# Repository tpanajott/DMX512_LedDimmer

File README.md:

# DMX512 Controller with remote LED drivers
This is a wireless DMX512 controller that will accept input of channel data via MQTT, web interface or manual control of a channel via button input. It has built in support for MQTT auto-registration in Home Assistant. The controller can take up to four inputs for buttons that can control 4 channels of DMX data. Each LED Driver board is configured to drive 350mA LEDs and each LED Driver board can be configured for a channel separately.

# Features
* Auto-registration of channels to Home Assistant via MQTT.
* Setup AP to configure parameters to connect to WiFi.
* Web interface to dynamically configured all settings without changing the code.
* Multiple buttons can control the same channel.
* Many settings for controlling dimming behaviour.
* Control of up to 4 different channels of lights.

# Settings
|Setting|Description|
|--------|-----------|
|Device name|Used as WiFi hostname, MQTT client name and as "device name" in Home Assistant.|
|Serial log level|The desired log level for serial output. Simply leave at "Error" or "None" when installed as no serial monitor will be there to capture it.|
|Connect to WiFi|The WiFi SSID (WiFi name) to connect to. Bu pressing the "List"-button a list of all available networks can be shown and a network selected.|
|WiFi Password|The password (PSK) for the chosen WiFi.|
|Minimum button press time|The time, in milliseconds, a button must have the same state before it is considered a press.|
|Time before dimming|The maximum time for a button to be considered a "press". If the button is still held after this amount if time the channel will start dimming.|

## Channel Settings
|Setting|Description|
|--------|-----------|
|Slider|The slider can be used to control brightness directly from the web interface.|
|Enabled|Wether the channel is in use or not.|
|Name|This is used as the light name in Home Assistant.|
|Channel|The DMX channel to send data on. This must match the "slave" card that is connected to the actual LEDs.|
|Minimum Level|Many LEDs simply don't light below to low a voltage. This setting will force at least the light level as the minimum. By using the slider for the channel and noting the value in "Current Output" this value can be found quiet easily.|
|Maximum Level|The maximum light level.|
|Dimming Speed|The time, in milliseconds, between each step up/down when dimming via a button input.|
|Auto-Dimming Speed|The time, in milliseconds, between each step up/down when dimming via web interface or MQTT.|
|Hold Period|The time, in milliseconds, to wait at min/max positions before switching direction and dimming again.|

## Button Settings
|Setting|Description|
|--------|-----------|
|Enabled|Used to enabling checking of button input.|
|Channel|This must match a configured channel in the "DMX Channels"-section. This is the DMX-channel to control.|

## MQTT Settings
|Setting|Description|
|--------|-----------|
|MQTT Server|The address to the MQTT server to be used.|
|MQTT Port|The port of the MQTT server.|
|MQTT Base Topic|The configured MQTT topic for Home Assistant to listen on. The default in Home Assistant is "homeassistant/".|
|Used MQTT authenticaion?|Check if using username and password for authentication to MQTT server.|
|MQTT Username|The username to use for login at the MQTT server.|
|MQTT Password|The password to use for login at the MQTT server.|

## Images
### Web Interface

### Controller board

### LED Driver board

## Bugs
* Input for Button 3 does not work. This needs a redesign of the PCB and for it to use an other GPIO input.

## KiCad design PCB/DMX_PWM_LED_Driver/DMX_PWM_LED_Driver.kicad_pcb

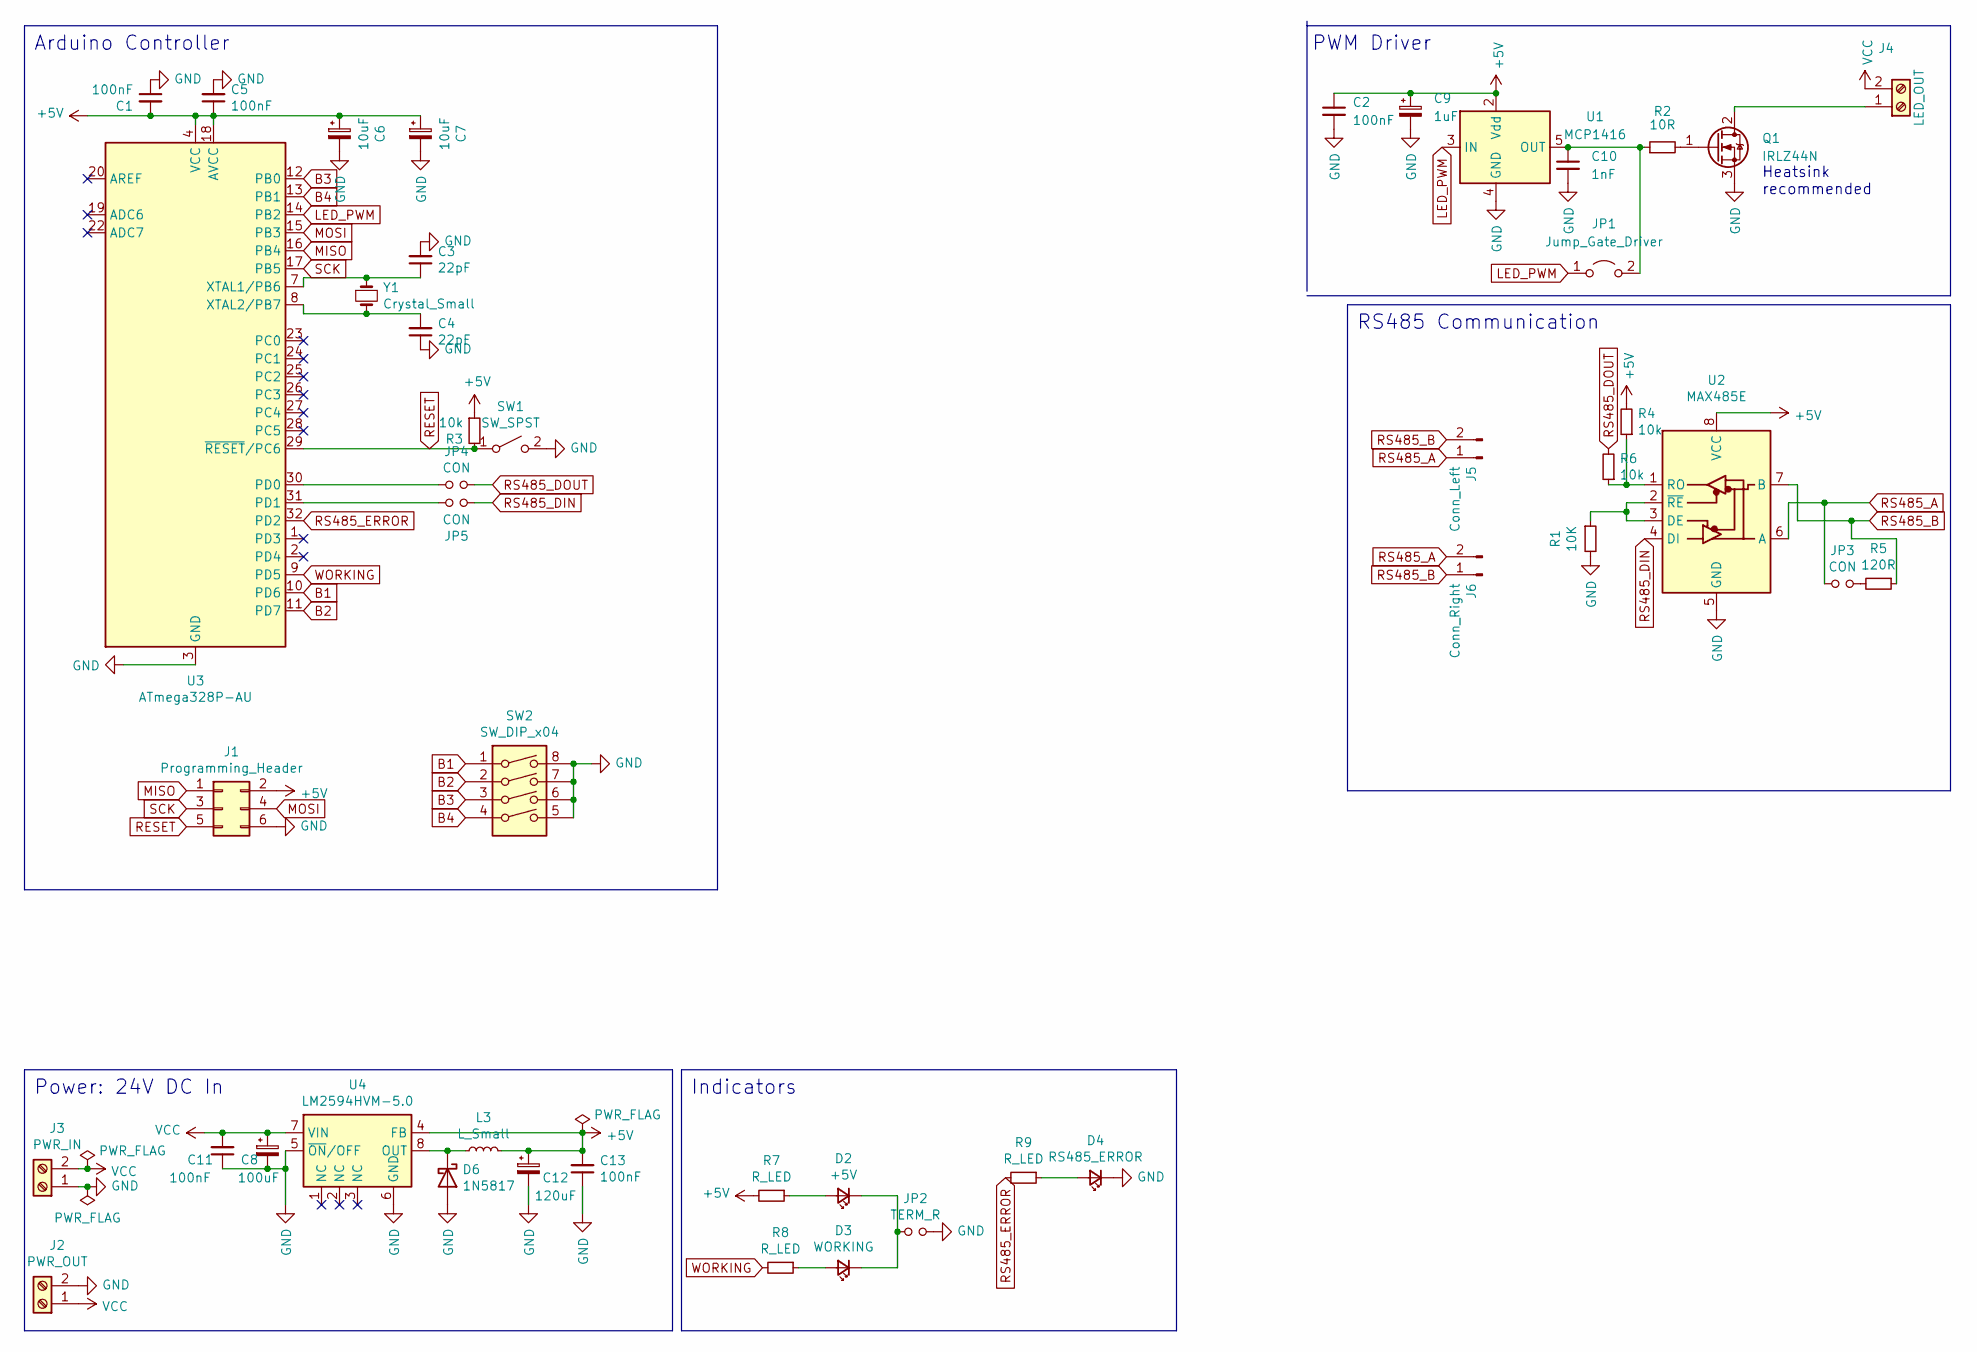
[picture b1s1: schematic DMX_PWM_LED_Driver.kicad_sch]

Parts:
C1, C5, C11, C13: 100nF; C_0805_2012Metric_Pad1.18x1.45mm_HandSolder; LCSC C49678
C2: 100nF; C_0805_2012Metric; LCSC C519929
C3, C4: 22pF; C_0805_2012Metric_Pad1.18x1.45mm_HandSolder; LCSC C24658
C6, C7: 10uF; CP_Radial_D4.0mm_P1.50mm; LCSC C694328
C8: 100uF; CP_Radial_D6.3mm_P2.50mm; LCSC C47859
C9: 1uF; CP_Radial_D5.0mm_P2.00mm; LCSC C62934
C10: 1nF; C_0603_1608Metric; LCSC C77026
C12: 120uF; CP_Radial_D8.0mm_P3.50mm; LCSC C178703
D2: +5V; D_1206_3216Metric_Pad1.42x1.75mm_HandSolder
D3: WORKING; D_1206_3216Metric_Pad1.42x1.75mm_HandSolder
D4: RS485_ERROR; D_1206_3216Metric_Pad1.42x1.75mm_HandSolder
D6: 1N5817; D_SOD-123; LCSC C727113
J1: Programming_Header; IDC-Header_2x03_P2.54mm_Vertical; LCSC C11214
J2: PWR_OUT; TerminalBlock_Phoenix_MKDS-1,5-2_1x02_P5.00mm_Horizontal; LCSC C8404
J3: PWR_IN; TerminalBlock_Phoenix_MKDS-1,5-2_1x02_P5.00mm_Horizontal; LCSC C8404
J4: LED_OUT; TerminalBlock_Phoenix_MKDS-1,5-2_1x02_P5.00mm_Horizontal; LCSC C8404
J5: Conn_Left; JST_XH_B2B-XH-A_1x02_P2.50mm_Vertical
J6: Conn_Right; JST_XH_B2B-XH-A_1x02_P2.50mm_Vertical
JP1: Jump_Gate_Driver; SolderJumper-2_P1.3mm_Open_Pad1.0x1.5mm
JP2: TERM_R; PinHeader_1x02_P2.54mm_Vertical; LCSC C234182
JP3, JP4, JP5: CON; PinHeader_1x02_P2.54mm_Vertical; LCSC C234182
L3: L_Small; L_6.3x6.3_H3; LCSC C206230
Q1: IRLZ44N; TO-220-3_Vertical
R1: 10K; R_0805_2012Metric_Pad1.20x1.40mm_HandSolder; LCSC C25612
R2: 10R; R_0805_2012Metric; LCSC C25278
R3, R4, R6: 10k; R_0805_2012Metric_Pad1.20x1.40mm_HandSolder; LCSC C25612
R5: 120R; R_0805_2012Metric_Pad1.20x1.40mm_HandSolder; LCSC C966144
R7, R8, R9: R_LED; R_1206_3216Metric_Pad1.30x1.75mm_HandSolder
SW1: SW_SPST; SW_Push_SPST_NO_Alps_SKRK
SW2: SW_DIP_x04; SW_DIP_SPSTx04_Slide_6.7x11.72mm_W8.61mm_P2.54mm_LowProfile; LCSC C54950
U1: MCP1416; SOT-23-5; LCSC C83775
U2: MAX485E; SOIC-8_3.9x4.9mm_P1.27mm; LCSC C19738
U3: ATmega328P-AU; TQFP-32_7x7mm_P0.8mm; LCSC C14877
U4: LM2594HVM-5.0; SOIC-8_3.9x4.9mm_P1.27mm; LCSC C179674
Y1: Crystal_Small; Crystal_HC49-U_Vertical; LCSC C16212

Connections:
+5V: C1.2, C2.1, C5.1, C6.1, C7.1, C9.1, C12.1, C13.2, J1.2, L3.2, R3.1, R4.2, R7.2, U1.2 (Vdd), U2.8 (VCC), U3.4 (VCC), U3.6 (VCC), U3.18 (AVCC), U4.4 (FB)
B1: SW2.1, U3.10 (PD6)
B2: SW2.2, U3.11 (PD7)
B3: SW2.3, U3.12 (PB0)
B4: SW2.4, U3.13 (PB1)
GND: C1.1, C2.2, C3.2, C4.1, C5.2, C6.2, C7.2, C8.2, C9.2, C10.2, C11.1, C12.2, C13.1, D4.1 (K), D6.2 (A), J1.6, J2.2, J3.1, JP2.2, Q1.3 (S), R1.2, SW1.2 (B), SW2.5, SW2.6, SW2.7, SW2.8, U1.4 (GND), U2.5 (GND), U3.3 (GND), U3.5 (GND), U3.21 (GND), U4.5 (~ON/OFF), U4.6 (GND)
LED_PWM: JP1.1 (A), U1.3 (IN), U3.14 (PB2)
MISO: J1.1, U3.16 (PB4)
MOSI: J1.4, U3.15 (PB3)
unnamed: C3.1, U3.7 (XTAL1/PB6), Y1.1
unnamed: C4.2, U3.8 (XTAL2/PB7), Y1.2
unnamed: C10.1, JP1.2 (B), R2.1, U1.5 (OUT)
unnamed: D2.1 (K), D3.1 (K), JP2.1
unnamed: D2.2 (A), R7.1
unnamed: D3.2 (A), R8.1
unnamed: D4.2 (A), R9.1
unnamed: D6.1 (K), L3.1, U4.8 (OUT)
unnamed: J4.1, Q1.2 (D)
unnamed: JP3.2, R5.2
unnamed: JP4.1, U3.30 (PD0)
unnamed: JP5.2, U3.31 (PD1)
unnamed: Q1.1 (G), R2.2
unnamed: R1.1, U2.2 (~RE), U2.3 (DE)
unnamed: R4.1, R6.1, U2.1 (RO)
RESET: J1.5, R3.2, SW1.1 (A), U3.29 (~RESET/PC6)
RS485_A: J5.1, J6.2, JP3.1, U2.6 (A)
RS485_B: J5.2, J6.1, R5.1, U2.7 (B)
RS485_DIN: JP5.1, U2.4 (DI)
RS485_DOUT: JP4.2, R6.2
RS485_ERROR: R9.2, U3.32 (PD2)
SCK: J1.3, U3.17 (PB5)
VCC: C8.1, C11.2, J2.1, J3.2, J4.2, U4.7 (VIN)
WORKING: R8.2, U3.9 (PD5)

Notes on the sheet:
RS485 Communication
Arduino Controller
Indicators
Power: 24V DC In
PWM Driver
Heatsink recommended

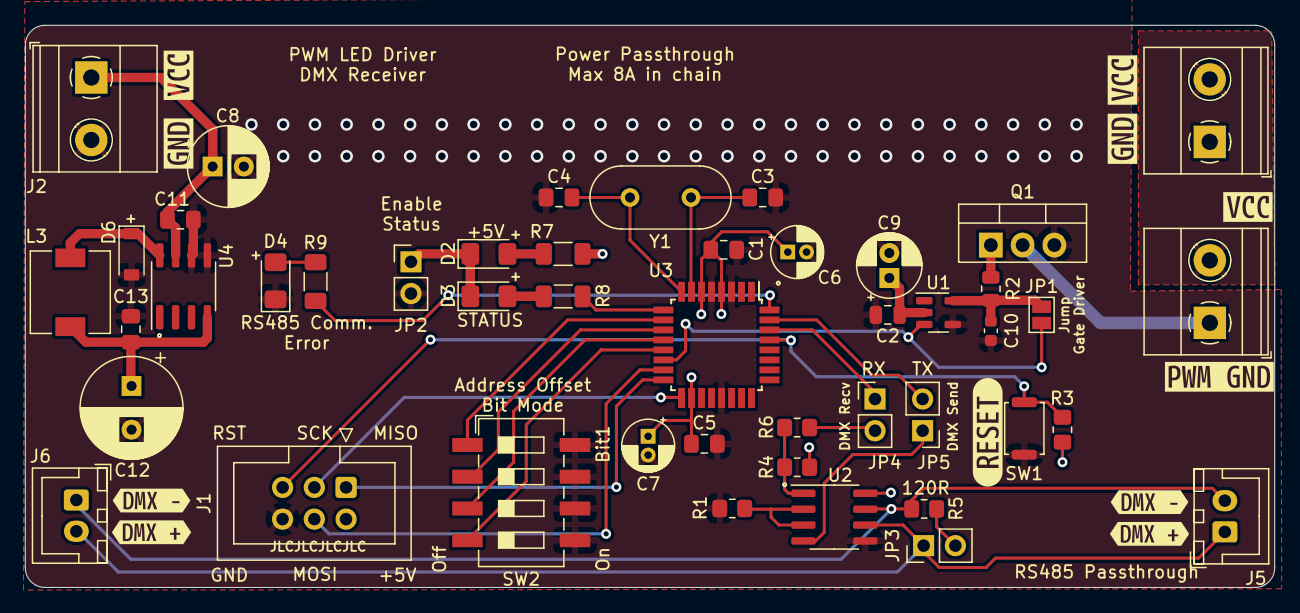
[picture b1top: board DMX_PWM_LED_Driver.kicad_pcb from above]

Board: 2 copper layers, 100.0 x 45.0 mm, 57 parts (0 on the bottom side), 33 nets.

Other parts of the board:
kibuzzard-63E822D9: G***; kibuzzard-63E822D9
kibuzzard-63E822E4, kibuzzard-63E822E4#2, kibuzzard-63E822E4#3: G***; kibuzzard-63E822E4
kibuzzard-63E8231D, kibuzzard-63E8231D#2: G***; kibuzzard-63E8231D
kibuzzard-63E8236A, kibuzzard-63E8236A#2: G***; kibuzzard-63E8236A
kibuzzard-63E8237A, kibuzzard-63E8237A#2: G***; kibuzzard-63E8237A
kibuzzard-63E8252B: G***; kibuzzard-63E8252B

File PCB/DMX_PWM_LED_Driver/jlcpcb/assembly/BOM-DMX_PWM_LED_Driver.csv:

Comment,Designator,Footprint,LCSC
Programming_Header,J1,IDC-Header_2x03_P2.54mm_Vertical,C11214
ATmega328P-AU,U3,TQFP-32_7x7mm_P0.8mm,C14877
Crystal_Small,Y1,Crystal_HC49-U_Vertical,C16212
120uF,C12,CP_Radial_D8.0mm_P3.50mm,C178703
LM2594HVM-5.0,U4,SOIC-8_3.9x4.9mm_P1.27mm,C179674
MAX485E,U2,SOIC-8_3.9x4.9mm_P1.27mm,C19738
L_Small,L3,L_6.3x6.3_H3,C206230
TERM_R,"JP2,JP3,JP4,JP5",PinHeader_1x02_P2.54mm_Vertical,C234182
22pF,"C3,C4",C_0805_2012Metric_Pad1.18x1.45mm_HandSolder,C24658
10R,R2,R_0805_2012Metric,C25278
10K,"R1,R3,R4,R6",R_0805_2012Metric_Pad1.20x1.40mm_HandSolder,C25612
100uF,C8,CP_Radial_D6.3mm_P2.50mm,C47859
100nF,"C1,C11,C13,C5",C_0805_2012Metric_Pad1.18x1.45mm_HandSolder,C49678
100nF,C2,C_0805_2012Metric,C519929
SW_DIP_x04,SW2,SW_DIP_SPSTx04_Slide_6.7x11.72mm_W8.61mm_P2.54mm_LowProfile,C54950
1uF,C9,CP_Radial_D5.0mm_P2.00mm,C62934
10uF,"C6,C7",CP_Radial_D4.0mm_P1.50mm,C694328
1N5817,D6,D_SOD-123,C727113
1nF,C10,C_0603_1608Metric,C77026
MCP1416,U1,SOT-23-5,C83775
PWR_OUT,"J2,J3,J4","TerminalBlock_Phoenix_MKDS-1,5-2_1x02_P5.00mm_Horizontal",C8404
120R,R5,R_0805_2012Metric_Pad1.20x1.40mm_HandSolder,C966144
SW_SPST,SW1,SW_Push_SPST_NO_Alps_SKRK,
Conn_Right,J6,JST_XH_B2B-XH-A_1x02_P2.50mm_Vertical,
Conn_Left,J5,JST_XH_B2B-XH-A_1x02_P2.50mm_Vertical,
R_LED,R9,R_1206_3216Metric_Pad1.30x1.75mm_HandSolder,
+5V,D2,D_1206_3216Metric_Pad1.42x1.75mm_HandSolder,
WORKING,D3,D_1206_3216Metric_Pad1.42x1.75mm_HandSolder,
R_LED,R7,R_1206_3216Metric_Pad1.30x1.75mm_HandSolder,
R_LED,R8,R_1206_3216Metric_Pad1.30x1.75mm_HandSolder,
RS485_ERROR,D4,D_1206_3216Metric_Pad1.42x1.75mm_HandSolder,
Jump_Gate_Driver,JP1,SolderJumper-2_P1.3mm_Open_Pad1.0x1.5mm,
IRLZ44N,Q1,TO-220-3_Vertical,

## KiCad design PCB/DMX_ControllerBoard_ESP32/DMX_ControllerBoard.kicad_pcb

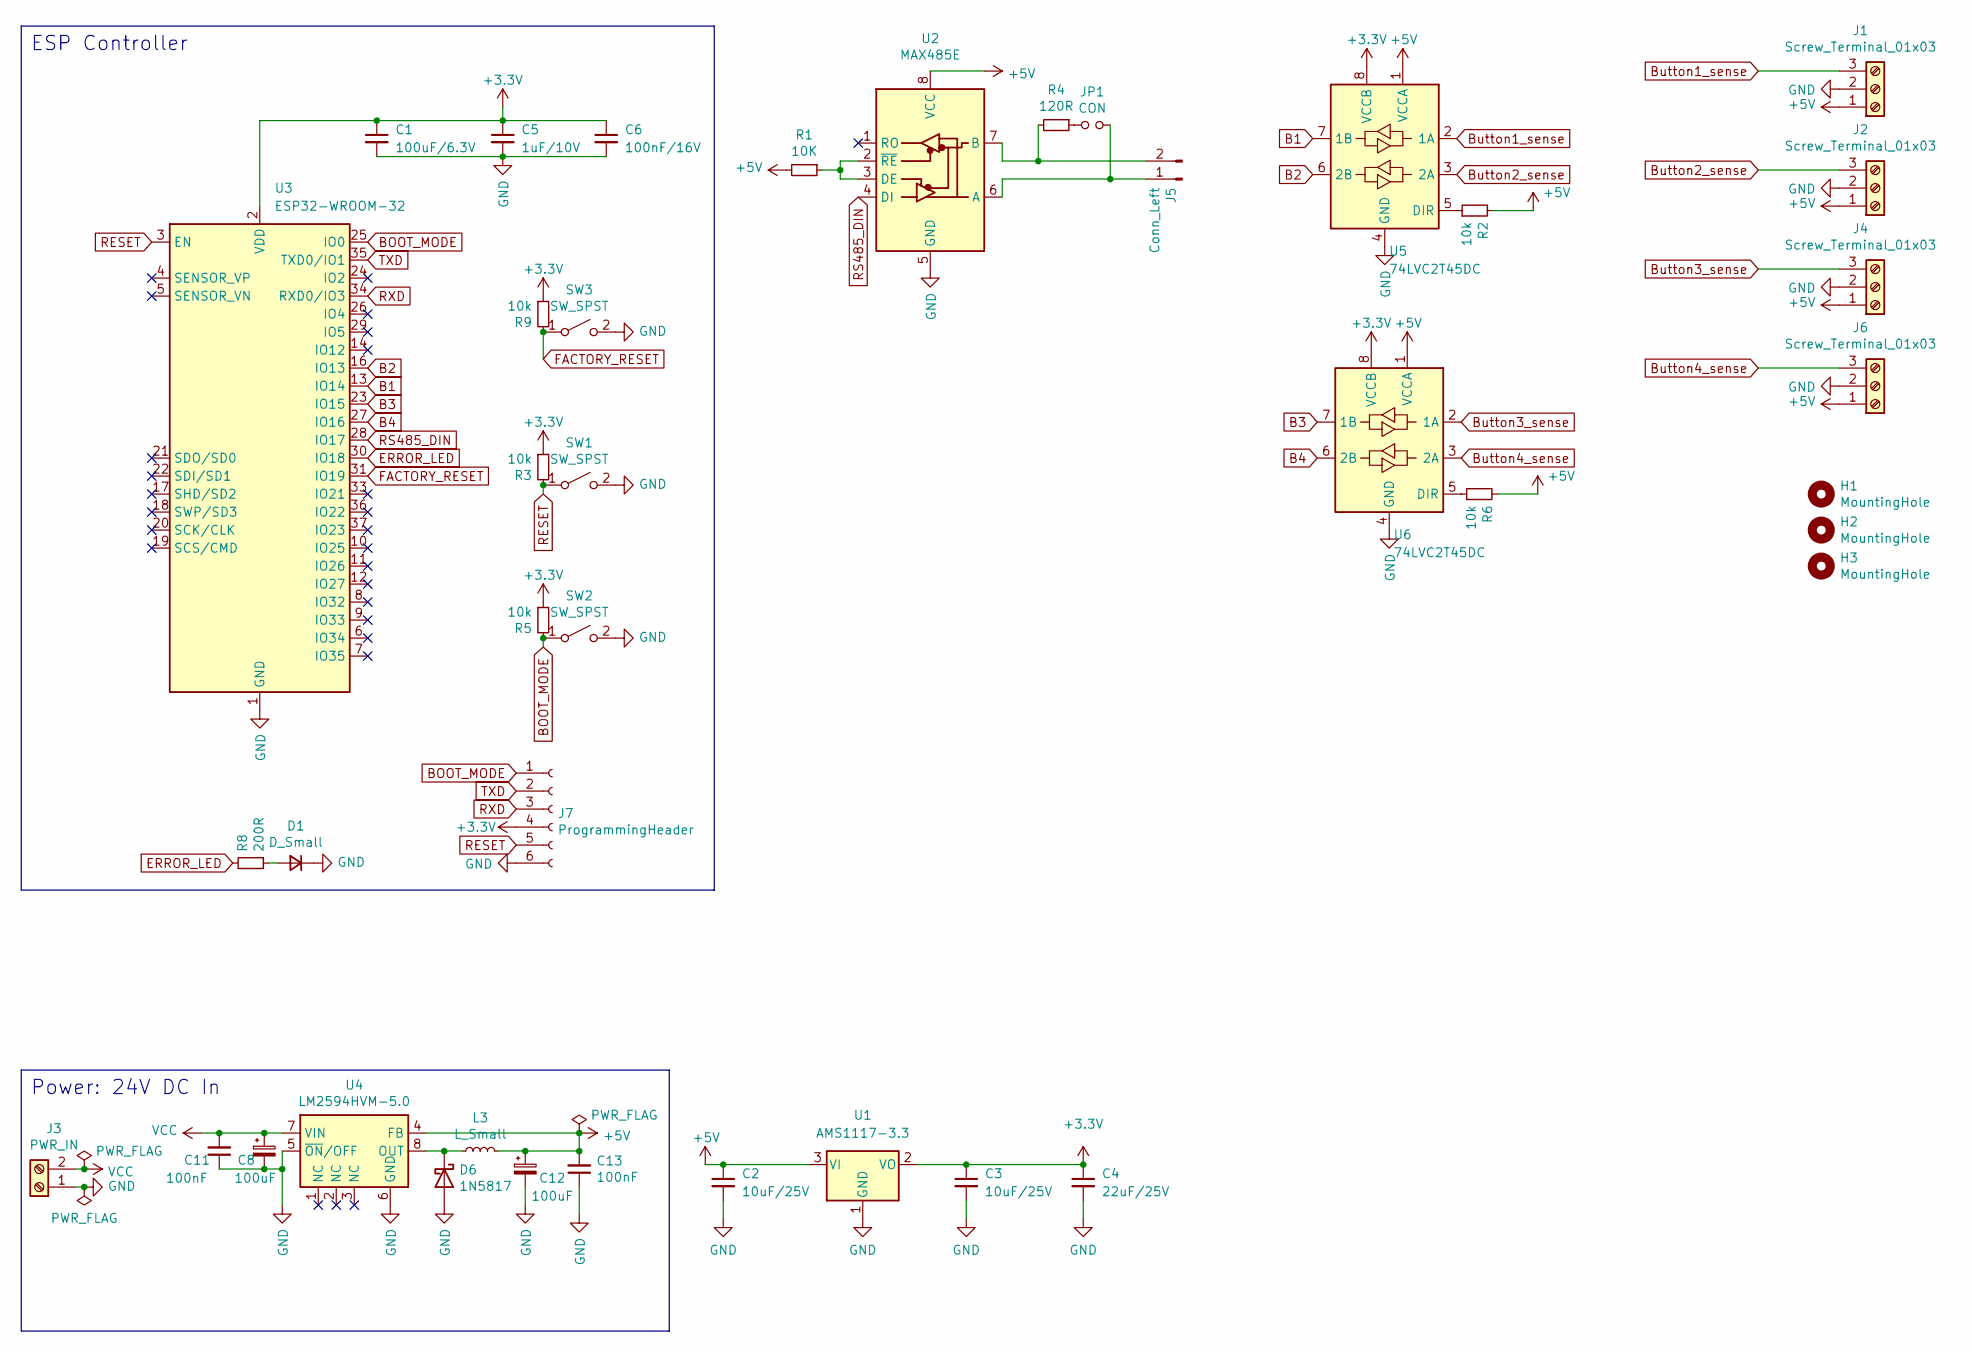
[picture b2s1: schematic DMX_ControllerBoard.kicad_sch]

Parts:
C1: 100uF/6.3V; C_1206_3216Metric; LCSC C15008
C2, C3: 10uF/25V; C_0805_2012Metric; LCSC C2922480
C4: 22uF/25V; C_0805_2012Metric; LCSC C602037
C5: 1uF/10V; C_0805_2012Metric; LCSC C92812
C6: 100nF/16V; C_0805_2012Metric; LCSC C519929
C8: 100uF; CP_Radial_D6.3mm_P2.50mm; LCSC C47859
C11, C13: 100nF; C_0805_2012Metric_Pad1.18x1.45mm_HandSolder; LCSC C49678
C12: 100uF; CP_Radial_D8.0mm_P3.50mm; LCSC C178703
D1: D_Small; D_1206_3216Metric_Pad1.42x1.75mm_HandSolder
D6: 1N5817; D_SOD-123; LCSC C727113
H1, H2, H3: MountingHole; MountingHole_3.2mm_M3
J1, J2, J4, J6: Screw_Terminal_01x03; TerminalBlock_Phoenix_MKDS-3-3-5.08_1x03_P5.08mm_Horizontal; LCSC C72334
J3: PWR_IN; TerminalBlock_Phoenix_MKDS-1,5-2_1x02_P5.00mm_Horizontal; LCSC C8404
J5: Conn_Left; JST_XH_B2B-XH-A_1x02_P2.50mm_Vertical
J7: ProgrammingHeader; PinSocket_1x06_P2.54mm_Vertical
JP1: CON; PinHeader_1x02_P2.54mm_Vertical; LCSC C234182
L3: L_Small; L_6.3x6.3_H3; LCSC C206230
R1: 10K; R_0805_2012Metric_Pad1.20x1.40mm_HandSolder; LCSC C25612
R2, R3, R5, R6, R9: 10k; R_0805_2012Metric_Pad1.20x1.40mm_HandSolder; LCSC C25612
R4: 120R; R_0805_2012Metric_Pad1.20x1.40mm_HandSolder; LCSC C966144
R8: 200R; R_1206_3216Metric_Pad1.30x1.75mm_HandSolder
SW1, SW2, SW3: SW_SPST; SW_Push_SPST_NO_Alps_SKRK
U1: AMS1117-3.3; SOT-223-3_TabPin2; LCSC C2891839
U2: MAX485E; SOIC-8_3.9x4.9mm_P1.27mm; LCSC C19738
U3: ESP32-WROOM-32
U4: LM2594HVM-5.0; SOIC-8_3.9x4.9mm_P1.27mm; LCSC C179674
U5, U6: 74LVC2T45DC; VSSOP-8_2.3x2mm_P0.5mm; LCSC C730237

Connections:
+3.3V: C1.1, C3.1, C4.1, C5.1, C6.1, J7.4, R3.1, R5.1, R9.1, U1.2 (VO), U3.2 (VDD), U5.8 (VCCB), U6.8 (VCCB)
+5V: C2.1, C12.1, C13.2, J1.1, J2.1, J4.1, J6.1, L3.2, R1.2, R2.2, R6.2, U1.3 (VI), U2.8 (VCC), U4.4 (FB), U5.1 (VCCA), U6.1 (VCCA)
B1: U3.13 (IO14), U5.7 (1B)
B2: U3.16 (IO13), U5.6 (2B)
B3: U3.23 (IO15), U6.7 (1B)
B4: U3.27 (IO16), U6.6 (2B)
BOOT_MODE: J7.1, R5.2, SW2.1 (A), U3.25 (IO0)
Button1_sense: J1.3, U5.2 (1A)
Button2_sense: J2.3, U5.3 (2A)
Button3_sense: J4.3, U6.2 (1A)
Button4_sense: J6.3, U6.3 (2A)
ERROR_LED: R8.2, U3.30 (IO18)
FACTORY_RESET: R9.2, SW3.1 (A), U3.31 (IO19)
GND: C1.2, C2.2, C3.2, C4.2, C5.2, C6.2, C8.2, C11.1, C12.2, C13.1, D1.1 (K), D6.2 (A), J1.2, J2.2, J3.1, J4.2, J6.2, J7.6, SW1.2 (B), SW2.2 (B), SW3.2 (B), U1.1 (GND), U2.5 (GND), U3.1 (GND), U3.15 (GND), U3.38 (GND), U3.39 (GND), U4.5 (~ON/OFF), U4.6 (GND), U5.4 (GND), U6.4 (GND)
unnamed: D1.2 (A), R8.1
unnamed: D6.1 (K), L3.1, U4.8 (OUT)
unnamed: J5.1, JP1.2, U2.6 (A)
unnamed: J5.2, R4.2, U2.7 (B)
unnamed: JP1.1, R4.1
unnamed: R1.1, U2.2 (~RE), U2.3 (DE)
unnamed: R2.1, U5.5 (DIR)
unnamed: R6.1, U6.5 (DIR)
RESET: J7.5, R3.2, SW1.1 (A), U3.3 (EN)
RS485_DIN: U2.4 (DI), U3.28 (IO17)
RXD: J7.3, U3.34 (RXD0/IO3)
TXD: J7.2, U3.35 (TXD0/IO1)
VCC: C8.1, C11.2, J3.2, U4.7 (VIN)

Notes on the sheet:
Power: 24V DC In
ESP Controller

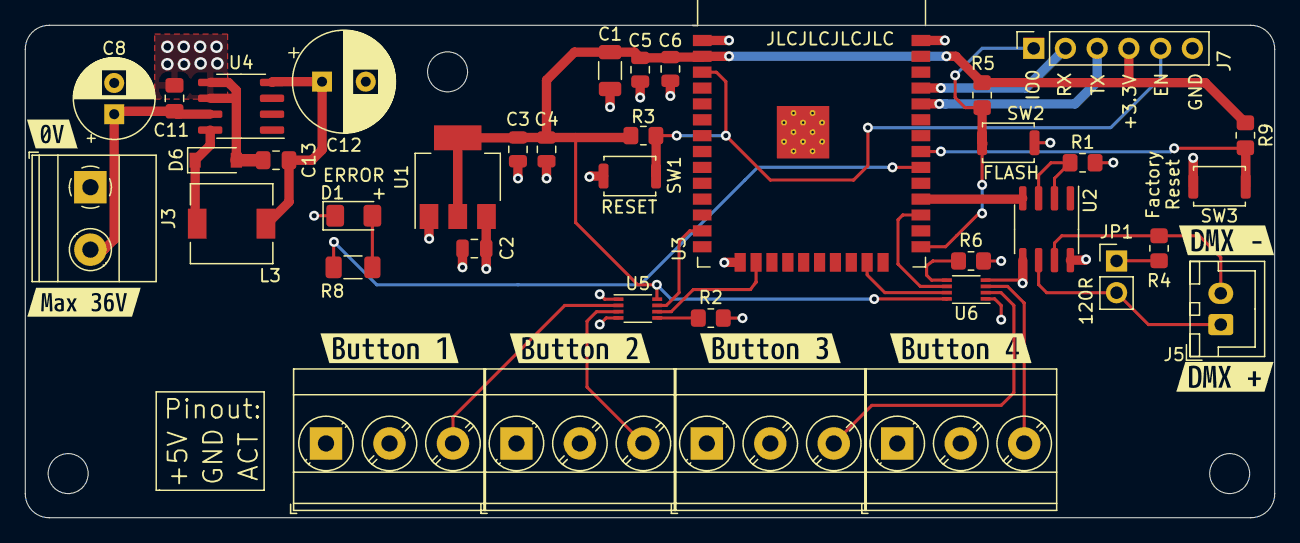
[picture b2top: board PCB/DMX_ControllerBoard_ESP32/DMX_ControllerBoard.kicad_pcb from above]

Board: 4 copper layers, 100.0 x 39.4 mm, 49 parts (0 on the bottom side), 27 nets.

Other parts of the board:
kibuzzard-63869B9D: G***; kibuzzard-63869B9D
kibuzzard-63869BC5: G***; kibuzzard-63869BC5
kibuzzard-63869BE0: G***; kibuzzard-63869BE0
kibuzzard-63869BE9: G***; kibuzzard-63869BE9
kibuzzard-638699ED: G***; kibuzzard-638699ED
kibuzzard-6386984B: G***; kibuzzard-6386984B
kibuzzard-63869759: G***; kibuzzard-63869759
kibuzzard-63869791: G***; kibuzzard-63869791

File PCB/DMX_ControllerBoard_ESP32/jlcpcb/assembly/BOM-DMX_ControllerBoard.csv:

Comment,Designator,Footprint,LCSC
100uF/6.3V,C1,C_1206_3216Metric,C15008
100uF,C12,CP_Radial_D8.0mm_P3.50mm,C178703
LM2594HVM-5.0,U4,SOIC-8_3.9x4.9mm_P1.27mm,C179674
MAX485E,U2,SOIC-8_3.9x4.9mm_P1.27mm,C19738
L_Small,L3,L_6.3x6.3_H3,C206230
CON,JP1,PinHeader_1x02_P2.54mm_Vertical,C234182
10K,"R1,R2,R3,R5,R6,R9",R_0805_2012Metric_Pad1.20x1.40mm_HandSolder,C25612
AMS1117-3.3,U1,SOT-223-3_TabPin2,C2891839
10uF/25V,"C2,C3",C_0805_2012Metric,C2922480
100uF,C8,CP_Radial_D6.3mm_P2.50mm,C47859
100nF,"C11,C13",C_0805_2012Metric_Pad1.18x1.45mm_HandSolder,C49678
100nF/16V,C6,C_0805_2012Metric,C519929
22uF/25V,C4,C_0805_2012Metric,C602037
Screw_Terminal_01x03,"J1,J2,J4,J6",TerminalBlock_Phoenix_MKDS-3-3-5.08_1x03_P5.08mm_Horizontal,C72334
1N5817,D6,D_SOD-123,C727113
74LVC2T45DC,"U5,U6",VSSOP-8_2.3x2mm_P0.5mm,C730237
PWR_IN,J3,"TerminalBlock_Phoenix_MKDS-1,5-2_1x02_P5.00mm_Horizontal",C8404
1uF/10V,C5,C_0805_2012Metric,C92812
120R,R4,R_0805_2012Metric_Pad1.20x1.40mm_HandSolder,C966144
Conn_Left,J5,JST_XH_B2B-XH-A_1x02_P2.50mm_Vertical,
SW_SPST,SW1,SW_Push_SPST_NO_Alps_SKRK,
ESP32-WROOM-32,U3,ESP32-WROOM-32,
D_Small,D1,D_1206_3216Metric_Pad1.42x1.75mm_HandSolder,
200R,R8,R_1206_3216Metric_Pad1.30x1.75mm_HandSolder,
SW_SPST,SW2,SW_Push_SPST_NO_Alps_SKRK,
ProgrammingHeader,J7,PinSocket_1x06_P2.54mm_Vertical,
SW_SPST,SW3,SW_Push_SPST_NO_Alps_SKRK,
MountingHole,H1,MountingHole_3.2mm_M3,
MountingHole,H2,MountingHole_3.2mm_M3,
MountingHole,H3,MountingHole_3.2mm_M3,

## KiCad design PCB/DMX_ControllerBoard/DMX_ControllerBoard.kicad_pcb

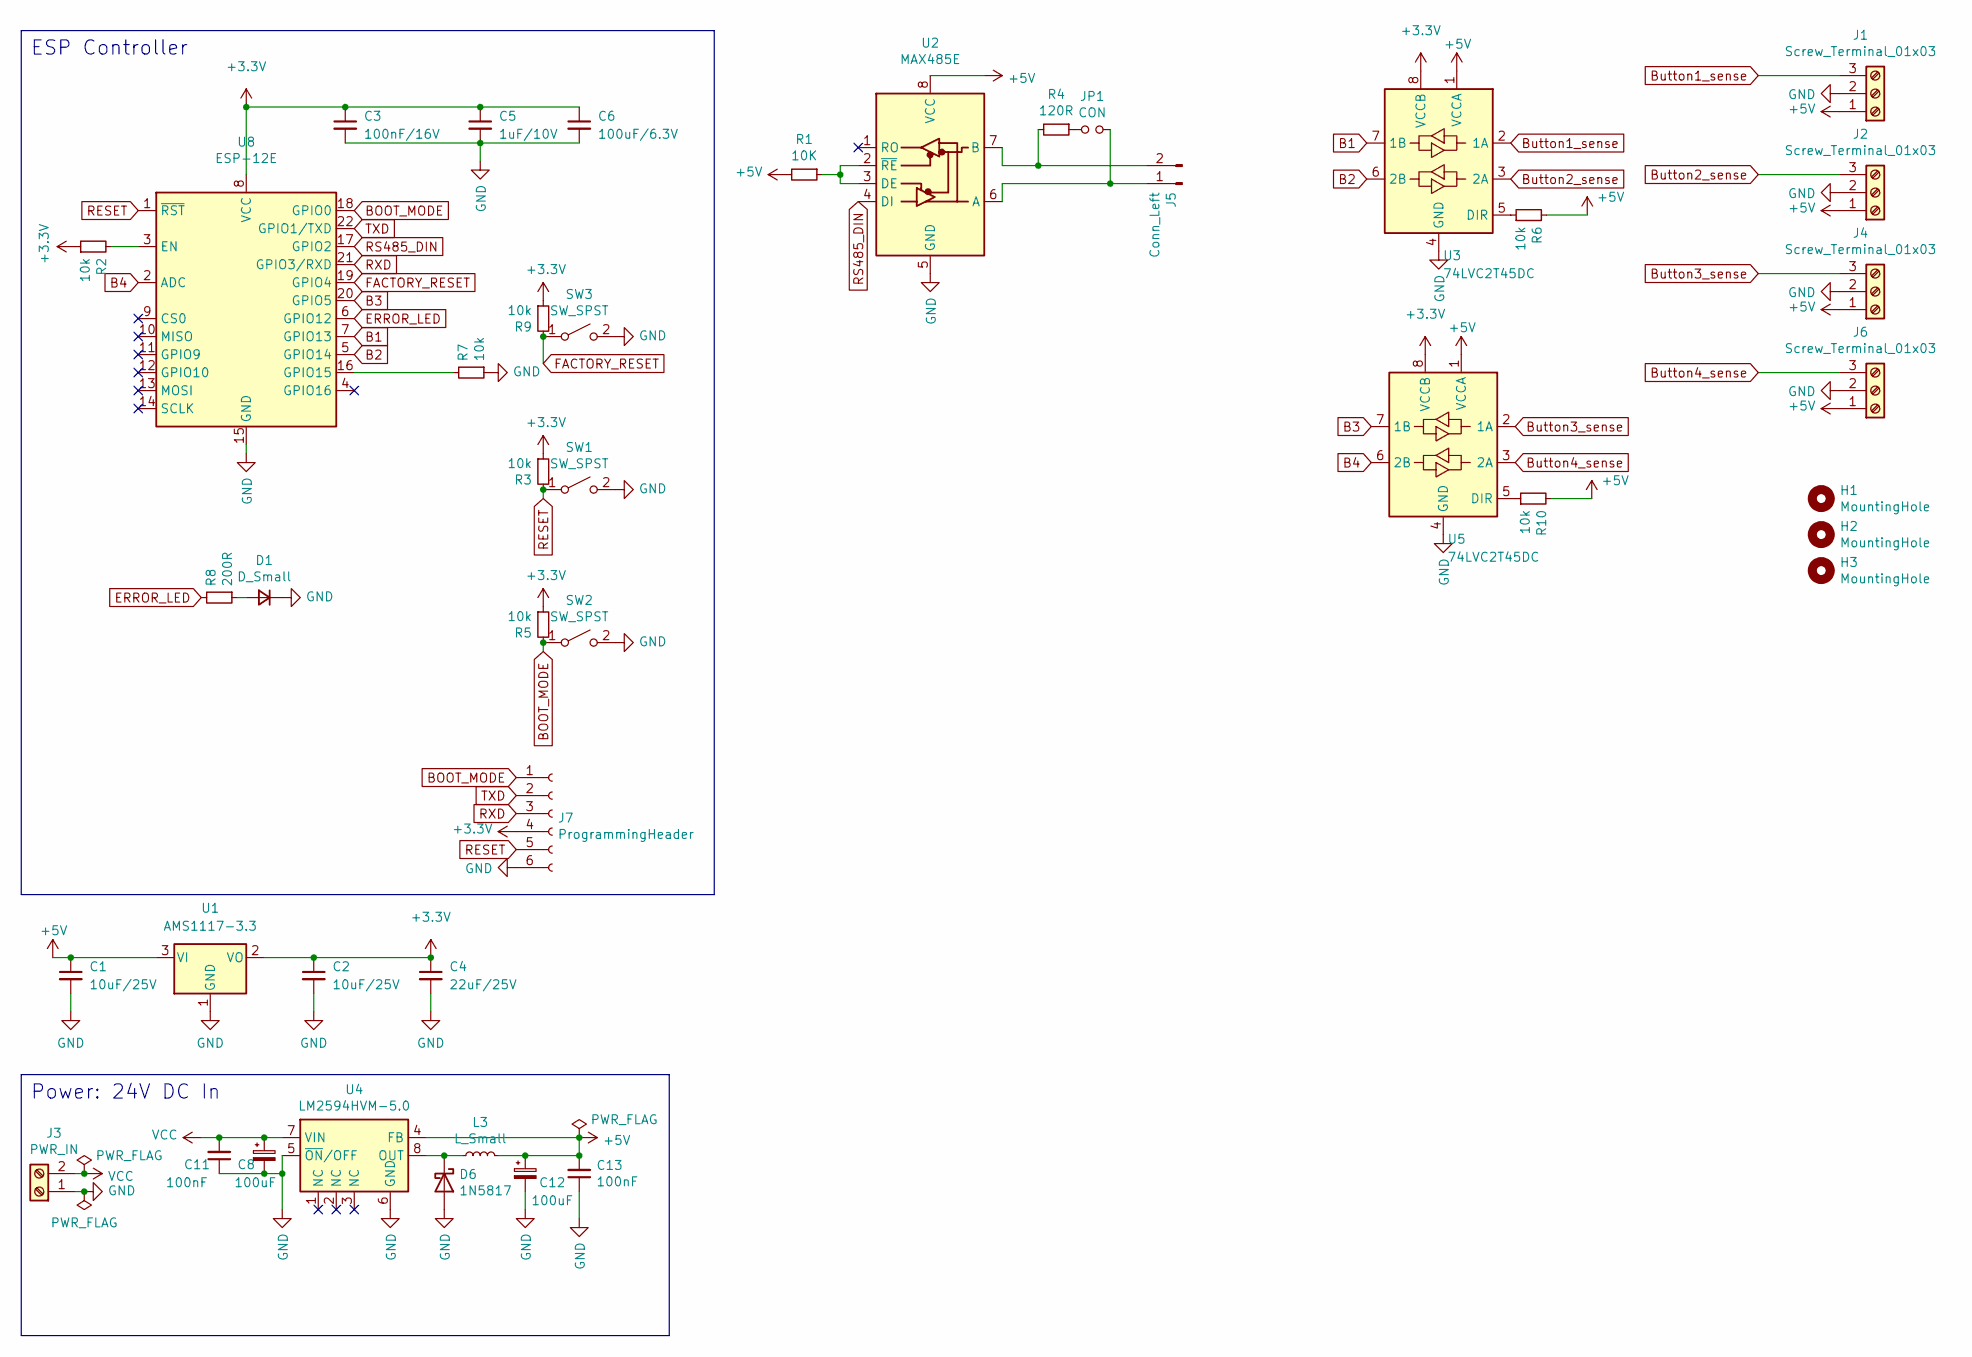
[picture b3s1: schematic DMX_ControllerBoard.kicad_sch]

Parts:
C1, C2: 10uF/25V; C_0805_2012Metric; LCSC C2922480
C3: 100nF/16V; C_0805_2012Metric; LCSC C519929
C4: 22uF/25V; C_0805_2012Metric; LCSC C602037
C5: 1uF/10V; C_0805_2012Metric; LCSC C92812
C6: 100uF/6.3V; C_1206_3216Metric; LCSC C15008
C8: 100uF; CP_Radial_D6.3mm_P2.50mm; LCSC C47859
C11, C13: 100nF; C_0805_2012Metric_Pad1.18x1.45mm_HandSolder; LCSC C49678
C12: 100uF; CP_Radial_D8.0mm_P3.50mm; LCSC C178703
D1: D_Small; D_1206_3216Metric_Pad1.42x1.75mm_HandSolder
D6: 1N5817; D_SOD-123; LCSC C727113
H1, H2, H3: MountingHole; MountingHole_3.2mm_M3
J1, J2, J4, J6: Screw_Terminal_01x03; TerminalBlock_Phoenix_MKDS-3-3-5.08_1x03_P5.08mm_Horizontal; LCSC C72334
J3: PWR_IN; TerminalBlock_Phoenix_MKDS-1,5-2_1x02_P5.00mm_Horizontal; LCSC C8404
J5: Conn_Left; JST_XH_B2B-XH-A_1x02_P2.50mm_Vertical
J7: ProgrammingHeader; PinSocket_1x06_P2.54mm_Vertical
JP1: CON; PinHeader_1x02_P2.54mm_Vertical; LCSC C234182
L3: L_Small; L_6.3x6.3_H3; LCSC C206230
R1: 10K; R_0805_2012Metric_Pad1.20x1.40mm_HandSolder; LCSC C25612
R2, R3, R5, R6, R7, R9, R10: 10k; R_0805_2012Metric_Pad1.20x1.40mm_HandSolder; LCSC C25612
R4: 120R; R_0805_2012Metric_Pad1.20x1.40mm_HandSolder; LCSC C966144
R8: 200R; R_1206_3216Metric_Pad1.30x1.75mm_HandSolder
SW1, SW2, SW3: SW_SPST; SW_Push_SPST_NO_Alps_SKRK
U1: AMS1117-3.3; SOT-223-3_TabPin2; LCSC C2891839
U2: MAX485E; SOIC-8_3.9x4.9mm_P1.27mm; LCSC C19738
U3, U5: 74LVC2T45DC; VSSOP-8_2.3x2mm_P0.5mm; LCSC C730237
U4: LM2594HVM-5.0; SOIC-8_3.9x4.9mm_P1.27mm; LCSC C179674
U8: ESP-12E; LCSC C89297

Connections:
+3V3: C2.1, C3.1, C4.1, C5.1, C6.1, J7.4, R2.1, R3.1, R5.1, R9.1, U1.2 (VO), U3.8 (VCCB), U5.8 (VCCB), U8.8 (VCC)
+5V: C1.1, C12.1, C13.2, J1.1, J2.1, J4.1, J6.1, L3.2, R1.2, R6.2, R10.2, U1.3 (VI), U2.8 (VCC), U3.1 (VCCA), U4.4 (FB), U5.1 (VCCA)
B1: U3.7 (1B), U8.7 (GPIO13)
B2: U3.6 (2B), U8.5 (GPIO14)
B3: U5.7 (1B), U8.20 (GPIO5)
B4: U5.6 (2B), U8.2 (ADC)
BOOT_MODE: J7.1, R5.2, SW2.1 (A), U8.18 (GPIO0)
Button1_sense: J1.3, U3.2 (1A)
Button2_sense: J2.3, U3.3 (2A)
Button3_sense: J4.3, U5.2 (1A)
Button4_sense: J6.3, U5.3 (2A)
ERROR_LED: R8.2, U8.6 (GPIO12)
FACTORY_RESET: R9.2, SW3.1 (A), U8.19 (GPIO4)
GND: C1.2, C2.2, C3.2, C4.2, C5.2, C6.2, C8.2, C11.1, C12.2, C13.1, D1.1 (K), D6.2 (A), J1.2, J2.2, J3.1, J4.2, J6.2, J7.6, R7.1, SW1.2 (B), SW2.2 (B), SW3.2 (B), U1.1 (GND), U2.5 (GND), U3.4 (GND), U4.5 (~ON/OFF), U4.6 (GND), U5.4 (GND), U8.15 (GND)
unnamed: D1.2 (A), R8.1
unnamed: D6.1 (K), L3.1, U4.8 (OUT)
unnamed: J5.1, JP1.2, U2.6 (A)
unnamed: J5.2, R4.2, U2.7 (B)
unnamed: JP1.1, R4.1
unnamed: R1.1, U2.2 (~RE), U2.3 (DE)
unnamed: R2.2, U8.3 (EN)
unnamed: R6.1, U3.5 (DIR)
unnamed: R7.2, U8.16 (GPIO15)
unnamed: R10.1, U5.5 (DIR)
RESET: J7.5, R3.2, SW1.1 (A), U8.1 (~RST)
RS485_DIN: U2.4 (DI), U8.17 (GPIO2)
RXD: J7.3, U8.21 (GPIO3/RXD)
TXD: J7.2, U8.22 (GPIO1/TXD)
VCC: C8.1, C11.2, J3.2, U4.7 (VIN)

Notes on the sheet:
Power: 24V DC In
ESP Controller

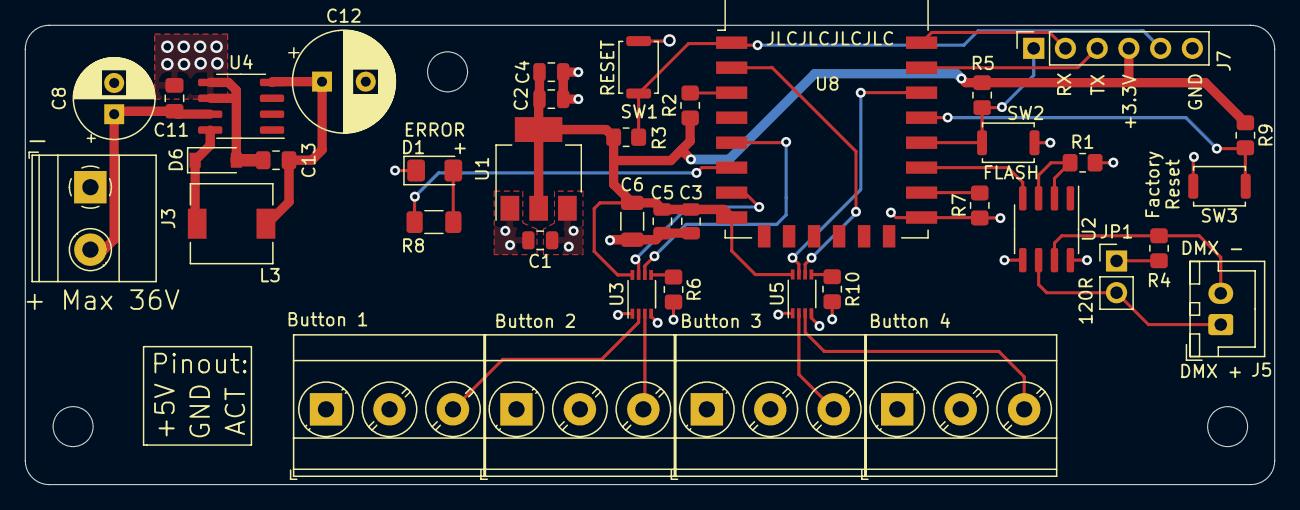
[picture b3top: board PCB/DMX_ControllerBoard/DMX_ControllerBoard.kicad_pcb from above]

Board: 4 copper layers, 100.0 x 36.8 mm, 43 parts (0 on the bottom side), 29 nets.

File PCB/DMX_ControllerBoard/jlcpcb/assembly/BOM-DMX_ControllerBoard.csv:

Comment,Designator,Footprint,LCSC
100uF/6.3V,C6,C_1206_3216Metric,C15008
100uF,C12,CP_Radial_D8.0mm_P3.50mm,C178703
LM2594HVM-5.0,U4,SOIC-8_3.9x4.9mm_P1.27mm,C179674
MAX485E,U2,SOIC-8_3.9x4.9mm_P1.27mm,C19738
L_Small,L3,L_6.3x6.3_H3,C206230
CON,JP1,PinHeader_1x02_P2.54mm_Vertical,C234182
10K,"R1,R10,R2,R3,R5,R6,R7,R9",R_0805_2012Metric_Pad1.20x1.40mm_HandSolder,C25612
AMS1117-3.3,U1,SOT-223-3_TabPin2,C2891839
10uF/25V,"C1,C2",C_0805_2012Metric,C2922480
100uF,C8,CP_Radial_D6.3mm_P2.50mm,C47859
100nF,"C11,C13",C_0805_2012Metric_Pad1.18x1.45mm_HandSolder,C49678
100nF/16V,C3,C_0805_2012Metric,C519929
22uF/25V,C4,C_0805_2012Metric,C602037
Screw_Terminal_01x03,"J1,J2,J4,J6",TerminalBlock_Phoenix_MKDS-3-3-5.08_1x03_P5.08mm_Horizontal,C72334
1N5817,D6,D_SOD-123,C727113
74LVC2T45DC,"U3,U5",VSSOP-8_2.3x2mm_P0.5mm,C730237
PWR_IN,J3,"TerminalBlock_Phoenix_MKDS-1,5-2_1x02_P5.00mm_Horizontal",C8404
ESP-12E,U8,ESP-12E,C89297
1uF/10V,C5,C_0805_2012Metric,C92812
120R,R4,R_0805_2012Metric_Pad1.20x1.40mm_HandSolder,C966144
Conn_Left,J5,JST_XH_B2B-XH-A_1x02_P2.50mm_Vertical,
SW_SPST,SW1,SW_Push_SPST_NO_Alps_SKRK,
D_Small,D1,D_1206_3216Metric_Pad1.42x1.75mm_HandSolder,
200R,R8,R_1206_3216Metric_Pad1.30x1.75mm_HandSolder,
SW_SPST,SW2,SW_Push_SPST_NO_Alps_SKRK,
ProgrammingHeader,J7,PinSocket_1x06_P2.54mm_Vertical,
SW_SPST,SW3,SW_Push_SPST_NO_Alps_SKRK,
MountingHole,H1,MountingHole_3.2mm_M3,
MountingHole,H2,MountingHole_3.2mm_M3,
MountingHole,H3,MountingHole_3.2mm_M3,

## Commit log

2022-01-19 Added .gitignore
2022-01-19 First commit of software for Controller and Slave card
2022-01-19 First commit of PCB design files
2022-01-19 Updated README and added 3D renders of the boards
2022-02-26 Fixed a bug where the SoftAP would start even though a SSID to connect to was configured
2022-08-06 Fixed a few bugs, added DEBUG flag in DimmerButton to be able to easily toggle debug serial print easy and increased the timeout from 5 to 10 seconds on the slave receiver
2022-08-06 Fixed a bug where, if a dimming target via MQTT was to set maximum or minimum brightness, when the physical button was pressed it would have to be pressed twice in order for it to reverse the directi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
2022-09-15 Added function to detect the number of channels in use and initialize the DMX library accordingly
2022-09-17 Started migration to new interrupt based light manager with tighter integration to other components
2022-09-17 Updated main.cpp to use LightManager instead of DimmerButtonManager
2022-09-17 Fixed bug where, if button was released on min or max before the holdPerios was over, the next dimming event would cause the light level to be set to min or max
2022-09-17 Updated to send MQTT status update on setting Auto dim target. Also changed to LOG_<LEVEL> logging instead of println and printf
2022-09-18 Will now only send status updates to web interface and via MQTT while not dimming. This results in a smoother dimming
2022-09-18 Transissioned from an array of dimmerButtons that were always populated with 4 buttons (even if only one was enabled) to a list with only the enabled buttons.
2022-09-18 Implemented smooth turn on/off
2022-10-01 Added function to select log level in the web interface
2022-10-01 Switched to my own custom logging library
2022-10-01 Fixed a bug where the calculated of number of DMX channels to initialize was one below required number
2022-10-02 Started work on finding power problems with original board and testing a new ESP32 board
2022-10-02 Added more labeling to ESP32 board
2022-10-10 Initial commit of ESP32 FreeRTOS implementation
2022-10-10 Initial commit of ESP32 based PCB
2022-10-10 Will now cancel any auto-dimming when dimming with the button starts
2022-10-11 Started initial work on getting the web interface back up and running
2022-10-15 MQTT control now implemented and some code cleanup
2022-10-15 Web interface now receives status updates and all data on connection
2022-10-15 It is now possible to control light output via web interface. Also included clamping of values to min/max for channel
2022-10-17 Final tests of software on PCB. Everything seems to be working
2022-10-17 Removed old ESP8266-based software and PCB. Will only support ESP32-based board going forward
2022-10-17 Updated images and README
2022-10-17 Added function to determine the highest DMX channel in use and initiate DMX-library accordingly
2022-10-19 Fixed various issues
2022-10-21 Fixed a bug where the wrong channel would be set on buttons. Also fixed a bug where a button press was not properly debounced and would make it basically impossible to turn off the light
2022-10-21 Updated README with setting-descriptions
2022-10-26 Updated ArduLog to version 1.1
2022-11-30 Switched from using iterators to using for loops by reference for clarity
2022-11-30 Updated labels on PCB for better readability
2022-11-30 Reverted back to polling button states as it seemed more stable Reverted back to not using retained MQTT messages and to instead listen for Home Assistant events and re-register as needed
2022-11-30 Added "reboot" button to start page
2022-11-30 Added more debugging information
2022-11-30 Added function to auto-generate a software version from git hash
2022-12-01 Recerted back to interruped based checking with more debounce checks
2022-12-01 Fixed vTaskDelays without specifying ms
2022-12-01 Fixed more vTaskDelays that were missing the "/ portTICK_PERIOD_MS"
2022-12-01 Fixed typo
2022-12-01 Fixed various small issues with handing data from web page
2022-12-01 Updated .gitignore
2022-12-03 Will skip debounce checking when button goes from confirmed PRESSED to DEPRESSED in order to not dim for a few more milliseconds and therfore not stopping at desiered level
2023-02-11 Started work on PWM LED Driver and fixed small spelling mistakes
2023-04-02 Updated design of PWM board and code updated for slave boards
